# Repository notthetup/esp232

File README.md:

# esp232
ESP32 + RS232 = 💰

This project is a simple PCB that allows you to connect an ESP32 to a RS232 port. The initial version is based on a Seeduino ESP32 Xiao board for simplicity.

## Features

- RS232 port with RTS/CTS flow control
- USB port for power and programming
- Seperate optional 5V power input
- Commonly available IDC connectors for connecting to RS232.

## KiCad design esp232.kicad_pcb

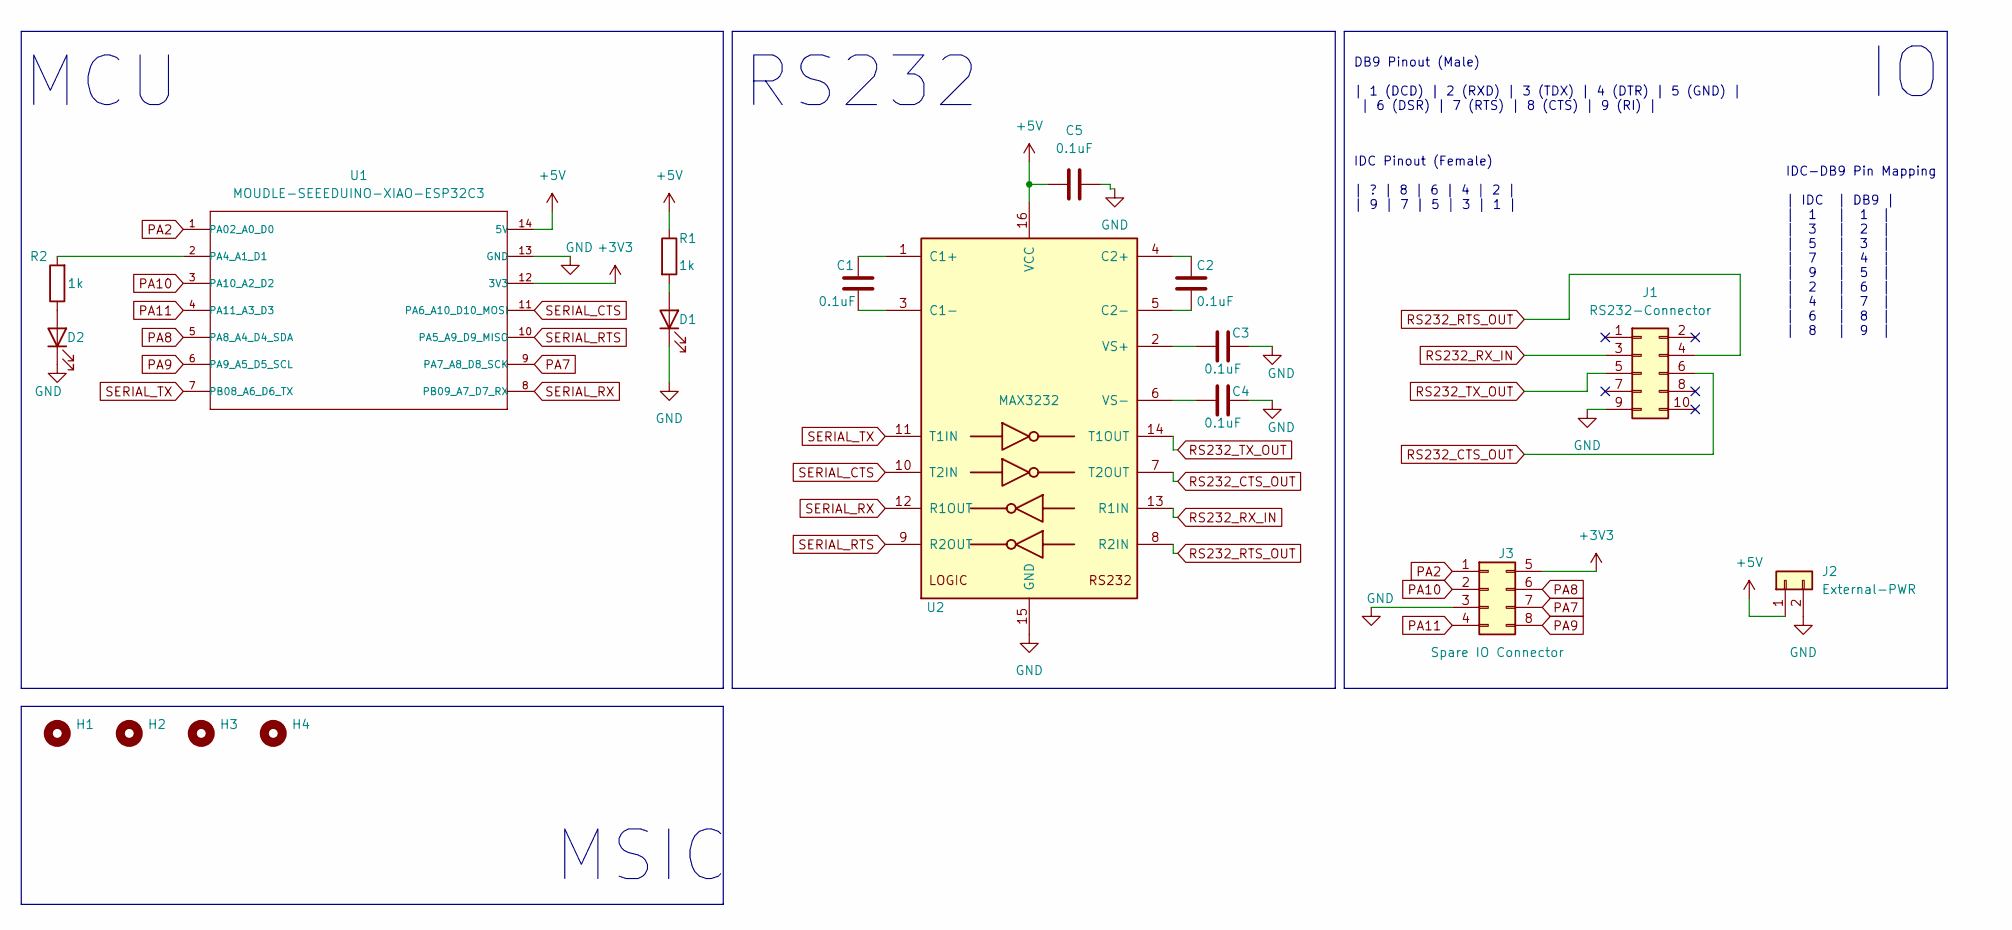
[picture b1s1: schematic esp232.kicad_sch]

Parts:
C1, C2, C3, C4, C5: 0.1uF; C_0805_2012Metric_Pad1.18x1.45mm_HandSolder
D1, D2: LED; LED_0805_2012Metric_Pad1.15x1.40mm_HandSolder
H1, H2, H3, H4: MountingHole; MountingHole_2.5mm
J1: RS232-Connector; IDC-Header_2x05_P2.54mm_Vertical
J2: External-PWR; PinHeader_1x02_P1.27mm_Vertical
J3: Spare IO Connector; PinHeader_2x04_P1.27mm_Vertical_SMD
R1, R2: 1k; R_0805_2012Metric_Pad1.20x1.40mm_HandSolder
U1: MOUDLE-SEEEDUINO-XIAO-ESP32C3; MOUDLE14P-SMD-2.54-21X17.8MM
U2: MAX3232; SOIC-16_3.9x9.9mm_P1.27mm

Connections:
+3V3: J3.5, U1.12 (3V3)
+5V: C5.1, J2.1, R1.1, U1.14 (5V), U2.16 (VCC)
GND: C3.2, C4.2, C5.2, D1.1 (K), D2.1 (K), J1.9, J2.2, J3.3, U1.13 (GND), U2.15 (GND)
unnamed: D1.2 (A), R1.2
unnamed: D2.2 (A), R2.1
unnamed: R2.2, U1.2 (PA4_A1_D1)
unnamed: C1.1, U2.1 (C1+)
unnamed: C1.2, U2.3 (C1-)
unnamed: C2.1, U2.4 (C2+)
unnamed: C2.2, U2.5 (C2-)
unnamed: C3.1, U2.2 (VS+)
unnamed: C4.1, U2.6 (VS-)
PA2: J3.1, U1.1 (PA02_A0_D0)
PA7: J3.7, U1.9 (PA7_A8_D8_SCK)
PA8: J3.6, U1.5 (PA8_A4_D4_SDA)
PA9: J3.8, U1.6 (PA9_A5_D5_SCL)
PA10: J3.2, U1.3 (PA10_A2_D2)
PA11: J3.4, U1.4 (PA11_A3_D3)
RS232_CTS_OUT: J1.6, U2.7 (T2OUT)
RS232_RTS_OUT: J1.4, U2.8 (R2IN)
RS232_RX_IN: J1.3, U2.13 (R1IN)
RS232_TX_OUT: J1.5, U2.14 (T1OUT)
SERIAL_CTS: U1.11 (PA6_A10_D10_MOSI), U2.10 (T2IN)
SERIAL_RTS: U1.10 (PA5_A9_D9_MISO), U2.9 (R2OUT)
SERIAL_RX: U1.8 (PB09_A7_D7_RX), U2.12 (R1OUT)
SERIAL_TX: U1.7 (PB08_A6_D6_TX), U2.11 (T1IN)

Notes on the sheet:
DB9 Pinout (Male) | 1 (DCD) | 2 (RXD) | 3 (TDX) | 4 (DTR) | 5 (GND) | | 6 (DSR) | 7 (RTS) | 8 (CTS) | 9 (RI) |
MCU
IDC Pinout (Female) | ? | 8 | 6 | 4 | 2 | | 9 | 7 | 5 | 3 | 1 |
IDC-DB9 Pin Mapping | IDC | DB9 | | 1 | 1 | | 3 | 2 | | 5 | 3 | | 7 | 4 | | 9 | 5 | | 2 | 6 | | 4 | 7 | | 6 | 8 | | 8 | 9 |
RS232
MSIC

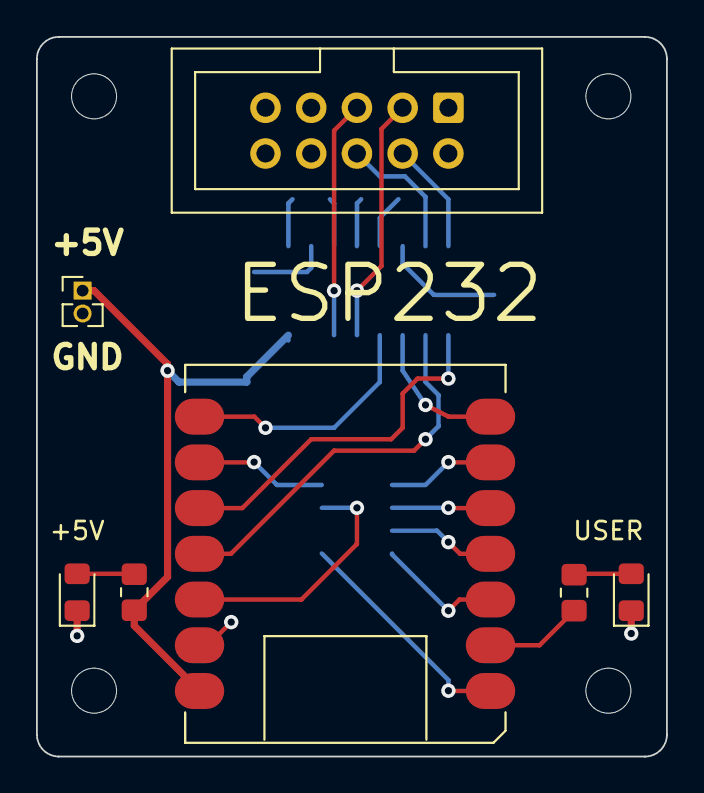
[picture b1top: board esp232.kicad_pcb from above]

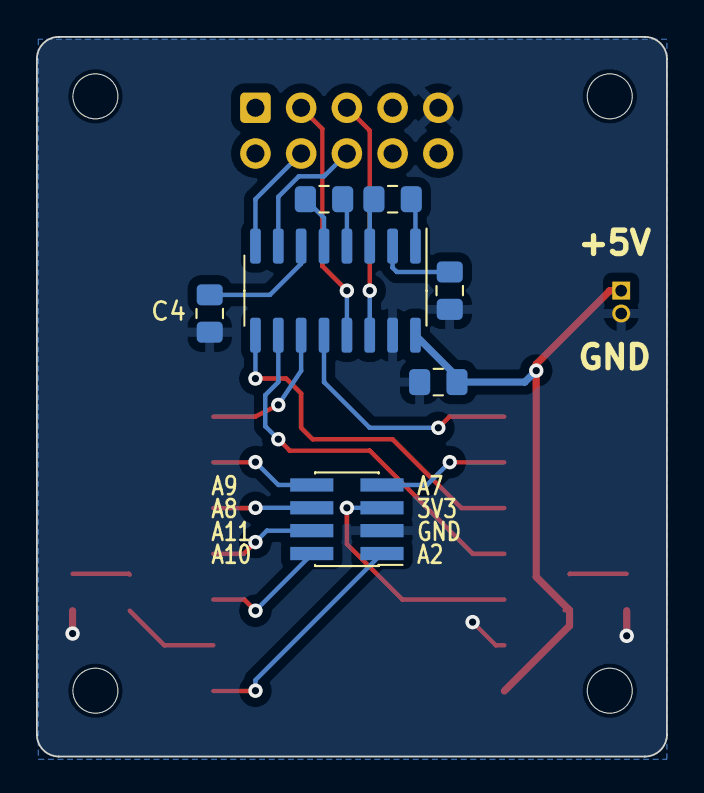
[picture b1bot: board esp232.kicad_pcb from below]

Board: 2 copper layers, 35.0 x 40.0 mm, 18 parts (7 on the bottom side), 26 nets.

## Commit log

2023-12-20 updated schematic and layout
2023-12-21 small layout improvements
2024-01-13 fixed review comments
2024-01-13 update gitignore
2024-03-13 updating firmware
2024-03-13 working micropython firmware
